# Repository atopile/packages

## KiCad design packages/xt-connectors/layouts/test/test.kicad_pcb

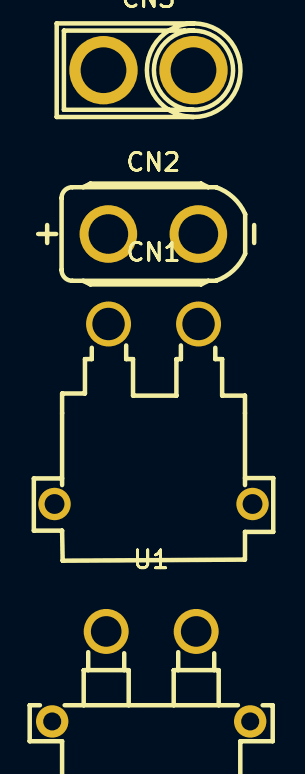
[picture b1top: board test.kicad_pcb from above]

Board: 2 copper layers, 4 parts (0 on the bottom side), 2 nets, no tracks yet.

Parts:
CN1: CONN-TH_XT30PW-M
CN2: CONN-TH_XT30UPB-F
CN3: CONN-TH_XT30U-M
U1: CONN-TH_XT30PW-F-1

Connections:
gnd: CN1.2, CN2.2, CN3.2, U1.2
hv: CN1.1, CN2.1, CN3.1, U1.1

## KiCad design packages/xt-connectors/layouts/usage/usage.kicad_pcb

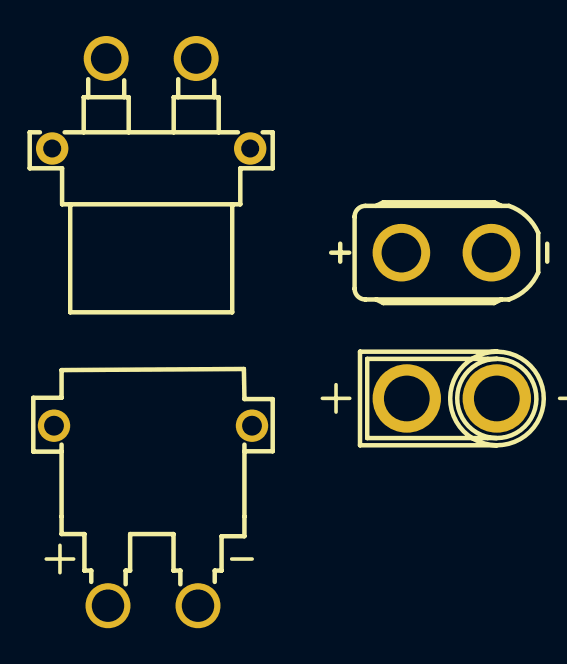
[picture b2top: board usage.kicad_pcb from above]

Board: 2 copper layers, 4 parts (0 on the bottom side), 2 nets, no tracks yet.

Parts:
CN1: CONN-TH_XT30PW-M
CN2: CONN-TH_XT30UPB-F
CN3: CONN-TH_XT30U-M
U1: CONN-TH_XT30PW-F-1

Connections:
hv: CN1.2, CN2.1, CN3.1, U1.1
lv: CN1.1, CN2.2, CN3.2, U1.2
